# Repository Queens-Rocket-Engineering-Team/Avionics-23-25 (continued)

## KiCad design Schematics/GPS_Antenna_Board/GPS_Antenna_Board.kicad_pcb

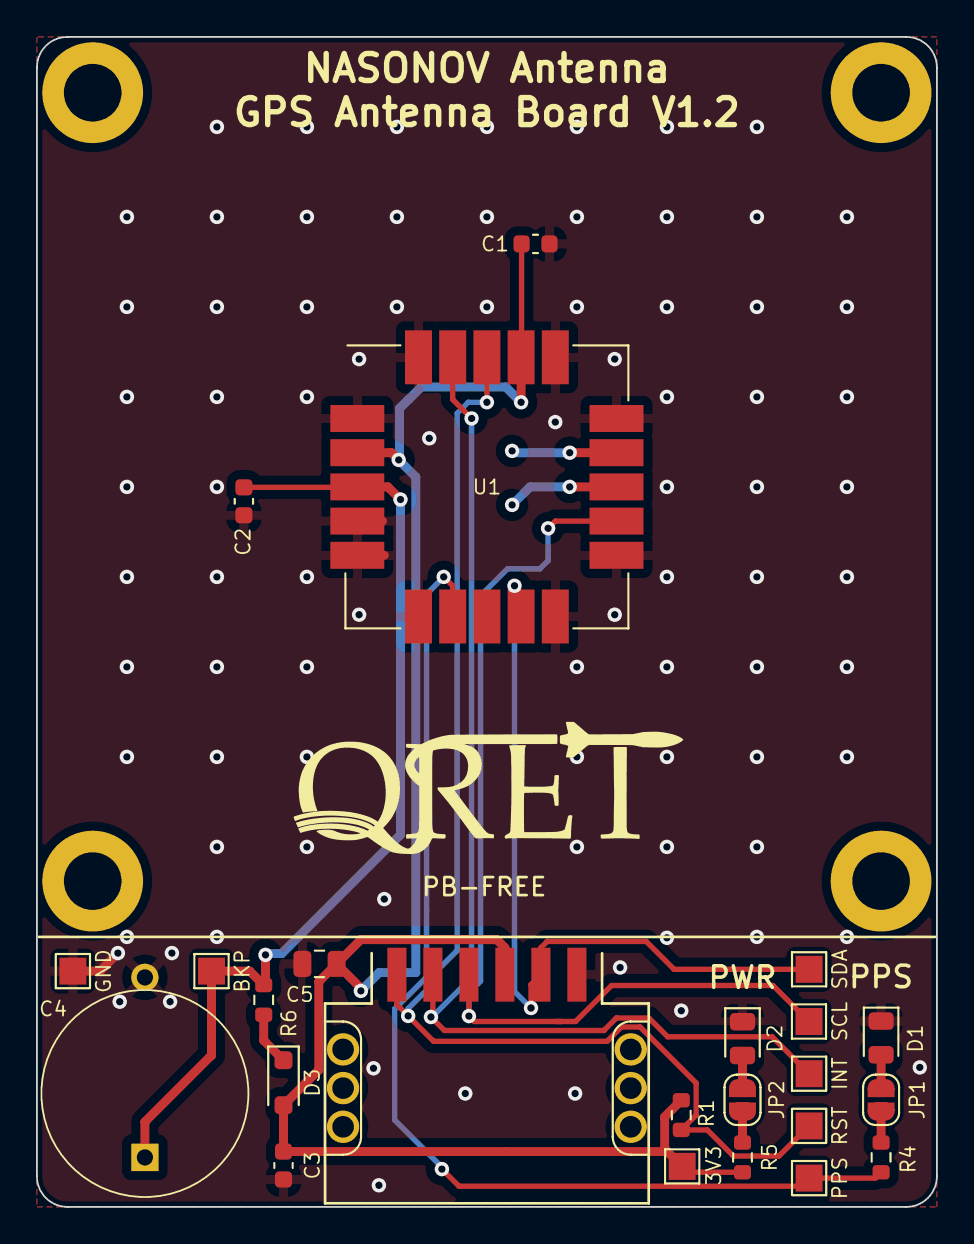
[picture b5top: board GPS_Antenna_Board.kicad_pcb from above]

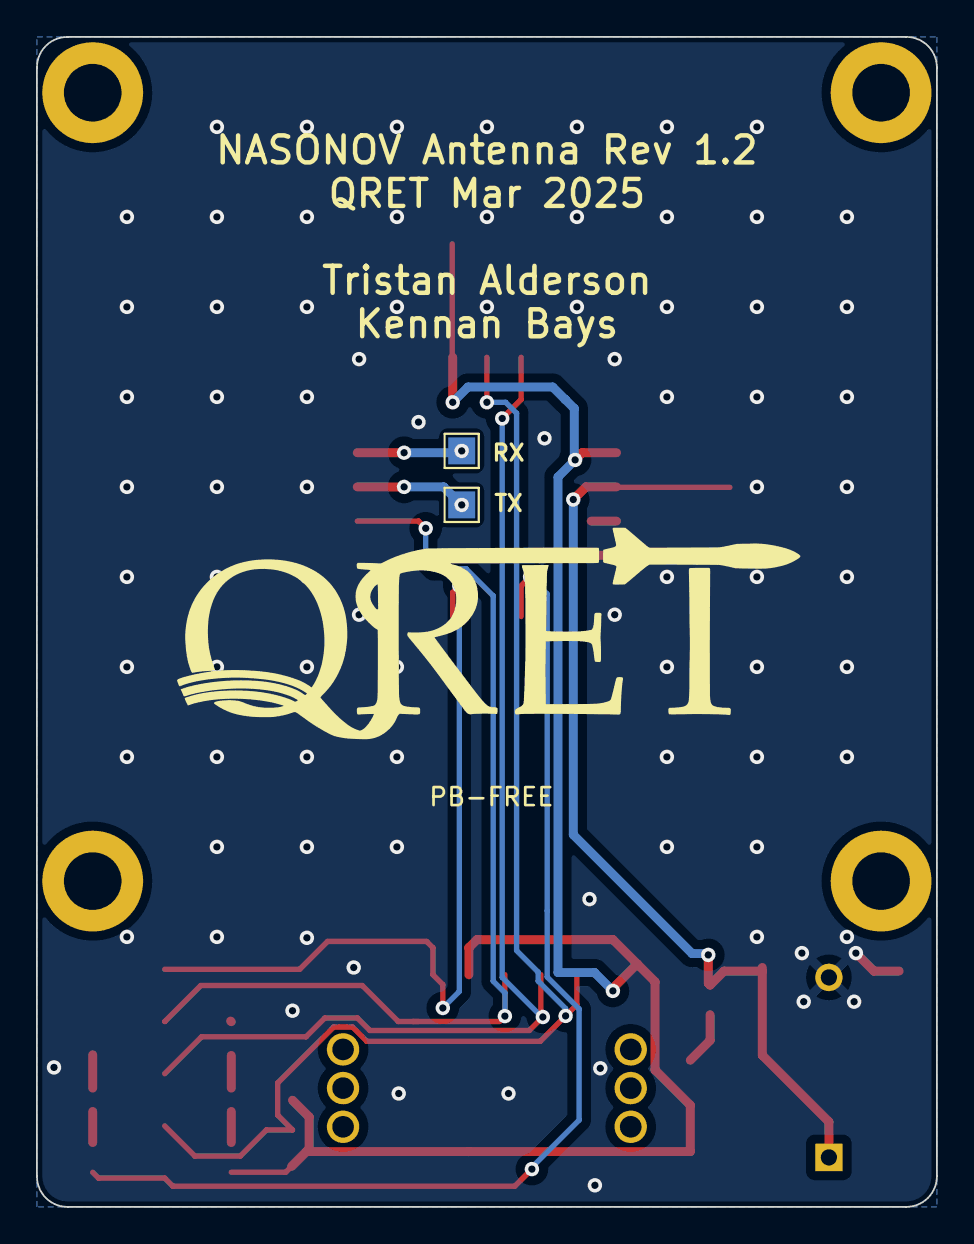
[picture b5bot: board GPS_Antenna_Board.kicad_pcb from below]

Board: 2 copper layers, 50.0 x 65.0 mm, 30 parts (2 on the bottom side), 15 nets.

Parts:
C1, C2: 100nF; C_0603_1608Metric
C3: 1uF; C_0603_1608Metric
C4: 330mF; CB5R5334HF-ZJP
C5: 47uF; C_0805_2012Metric
D1: White; LED_0805_2012Metric
D2: Green; LED_0805_2012Metric
D3: 1N5819WS; D_SOD-323_HandSoldering
H1, H2, H3, H4: MountingHole; MountingHole_3.2mm_M3_DIN965_Pad
J1: GT8E-6P-2H(55); CONN_GT8E-6P-2H(55)
JP1: ENA_PPS_LED; SolderJumper-2_P1.3mm_Open_RoundedPad1.0x1.5mm
JP2: ENA_PWR_LED; SolderJumper-2_P1.3mm_Open_RoundedPad1.0x1.5mm
R1: 10k; R_0603_1608Metric
R4: 2.2k; R_0603_1608Metric
R5: 3.3k; R_0603_1608Metric
R6: 100R; R_0603_1608Metric
TP1: GND; TestPoint_Pad_1.5x1.5mm
TP2: SCL; TestPoint_Pad_1.5x1.5mm
TP3: SDA; TestPoint_Pad_1.5x1.5mm
TP4: BKP; TestPoint_Pad_1.5x1.5mm
TP5: RST; TestPoint_Pad_1.5x1.5mm
TP6: INT; TestPoint_Pad_1.5x1.5mm
TP7: PPS; TestPoint_Pad_1.5x1.5mm
TP8: 3V3; TestPoint_Pad_1.5x1.5mm
TP9: RX; TestPoint_Pad_1.5x1.5mm
TP10: TX; TestPoint_Pad_1.5x1.5mm
U1: SAM-M10Q; ublox_SAM-M8Q_HandSolder

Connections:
+3.3V: C1.2, C3.1, C5.2, D3.2 (A), J1.3, R1.1, R5.1, TP8.1, U1.2 (VCC_IO), U1.17 (VCC)
BCKP_BATT: C2.2, C4.1, R6.2, TP4.1, U1.3 (V_BCKP)
GND: C1.1, C2.1, C3.2, C4.2, C5.1, D1.1 (K), D2.1 (K), J1.1, TP1.1, U1.1 (GND), U1.4 (GND), U1.5 (GND), U1.6 (GND), U1.10 (GND), U1.11 (GND), U1.15 (GND), U1.16 (GND), U1.20 (GND)
GPS_EXTINT: J1.5, TP6.1, U1.19 (EXTINT)
GPS_PPS: R4.1, TP7.1, U1.7 (TIMEPULSE)
GPS_RST: J1.6, R1.2, TP5.1, U1.18 (~RESET)
unnamed: D1.2 (A), JP1.1 (A)
unnamed: D2.2 (A), JP2.1 (A)
unnamed: D3.1 (K), R6.1
unnamed: JP1.2 (B), R4.2
unnamed: JP2.2 (B), R5.2
unnamed: TP9.1, U1.14 (RXD)
unnamed: TP10.1, U1.13 (TXD)
SCL: J1.4, TP2.1, U1.12 (SCL)
SDA: J1.2, TP3.1, U1.9 (SDA)

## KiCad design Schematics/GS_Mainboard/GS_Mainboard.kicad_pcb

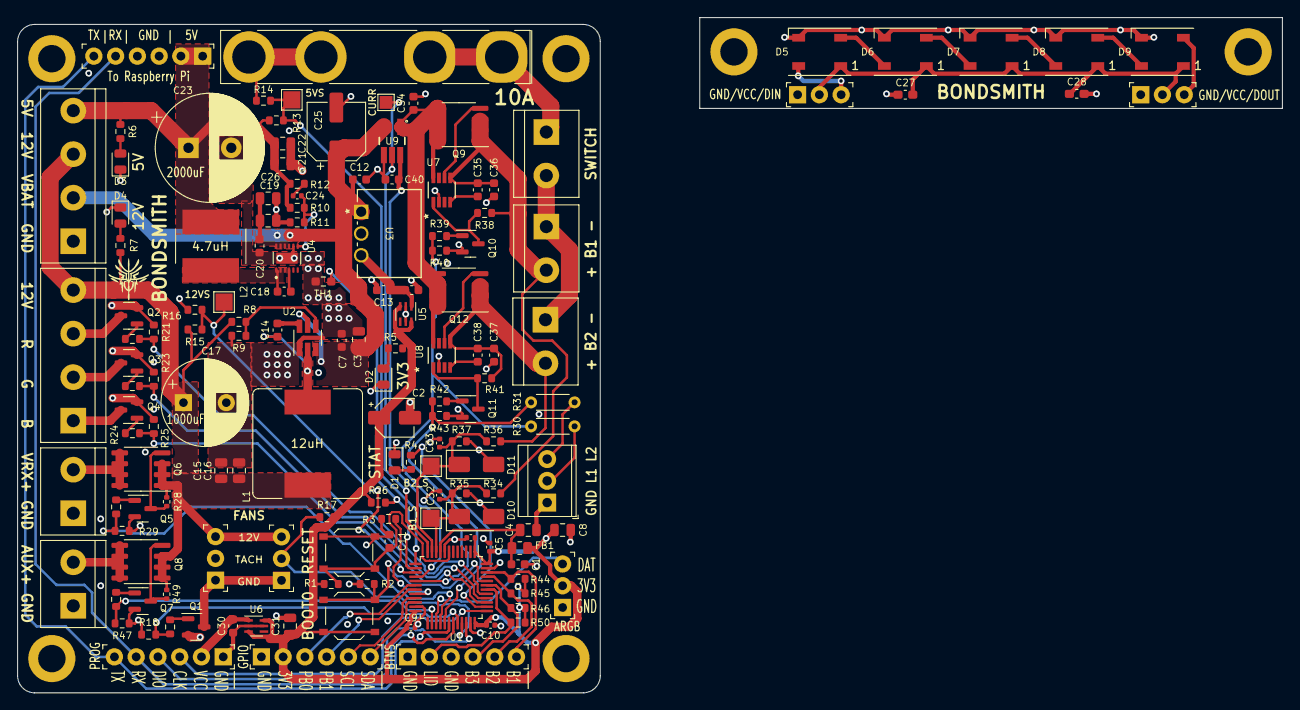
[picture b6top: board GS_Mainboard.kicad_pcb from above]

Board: 4 copper layers, 68.0 x 78.0 mm, 154 parts (0 on the bottom side), 89 nets.

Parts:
C1: 10n; C_0603_1608Metric
C2: 10uF; CP_Elec_4x5.4
C3, C19: 4.7uF; C_0805_2012Metric
C4, C8: 1uF; C_0805_2012Metric
C5, C6, C9, C10, C32, C33: 100n; C_0402_1005Metric
C7, C11, C14, C18, C20: 100nF; C_0603_1608Metric
C12: 10uF; C_0603_1608Metric
C13: 22uF; C_0603_1608Metric
C15, C16: 22uF; C_0805_2012Metric
C17: 1000uF, 25V; CP_Radial_D10.0mm_P5.00mm
C21, C22, C26, C31: 47uF; C_0805_2012Metric
C23: 2000uF, 25V; CP_Radial_D12.5mm_P5.00mm
C24: 33pF; C_0402_1005Metric
C25: 100uF; CP_Elec_6.3x5.9
C27, C28: 2.2uF; C_0603_1608Metric_Pad1.08x0.95mm_HandSolder
C29, C30, C34, C35, C36, C37, C38: 1uF; C_0603_1608Metric
C40: 0.1u; C_0603_1608Metric
D1: DB_LED (YLW); LED_0805_2012Metric
D2: 3.3V PWR (GRN); LED_0805_2012Metric
D3: 5.0V PWR (GRN); LED_0805_2012Metric
D4: 12V PWR (GRN); LED_0805_2012Metric
D5, D6, D7, D8, D9: WS2812B; LED_WS2812B_PLCC4_5.0x5.0mm_P3.2mm
D10, D11: SS54; D_SMA
F1: ATC Fuse; Fuseholder_Keystone_3555-2
FB1: 100R; R_0805_2012Metric
H1, H2, H3, H4, H5, H6: MountingHole; MountingHole_3.2mm_M3_ISO14580_Pad
J1: SWD Header; PinHeader_1x6_P2.54mm_Drill1.02mm
J2: RASPI; PinHeader_1x6_P2.54mm_Drill1.02mm
J3: ARGB_OUT; PinHeader_1x3_P2.54mm_Drill1.02mm
J4: RGB_IN; PinHeader_1x3_P2.54mm_Drill1.02mm
J5: RGB_OUT; PinHeader_1x3_P2.54mm_Drill1.02mm
J6: FAN1; PinHeader_1x3_P2.54mm_Drill1.02mm
J7: FAN2; PinHeader_1x3_P2.54mm_Drill1.02mm
J8: RGB12V; TerminalBlock_bornier-4_P5.08mm
J9: RTX_PWR; TerminalBlock_bornier-2_P5.08mm
J10: GPIO; PinHeader_1x6_P2.54mm_Drill1.02mm
J11: AUX_PWR; TerminalBlock_bornier-2_P5.08mm
J12: SRC_IND; TerminalBlock_TE_282834-3_1x03_P2.54mm_Horizontal
J13: BATT1; TerminalBlock_bornier-2_P5.08mm
J14: BATT2; TerminalBlock_bornier-2_P5.08mm
J15: SWITCH; TerminalBlock_bornier-2_P5.08mm
J16: BUTTS; PinHeader_1x6_P2.54mm_Drill1.02mm
J17: POWER; TerminalBlock_bornier-4_P5.08mm
L1: 12uH; L_Bourns_SRR1260
L2: 4.7uH; L_Bourns_SRN8040TA
Q1, Q2, Q3, Q4, Q5, Q7, Q10, Q11: AO3400A; SOT-23
Q6, Q8: AO4447A; SOIC-8_3.9x4.9mm_P1.27mm
Q9, Q12: AO4406A; SOIC-8_3.9x4.9mm_P1.27mm
R1, R17, R26, R35, R37, R38, R41, R44, R45, R46, R50: 10k; R_0603_1608Metric
R2, R3, R18, R21, R23, R25, R29, R40, R43, R47: 100k; R_0603_1608Metric
R4: 680R; R_0603_1608Metric
R5: 3.3k; R_0603_1608Metric
R6: 15k; R_0603_1608Metric
R7, R8: 68k; R_0603_1608Metric
R9: 3.6k; R_0603_1608Metric
R10: 33k; R_0603_1608Metric
R11: 6.2k; R_0603_1608Metric
R12: 1k; R_0603_1608Metric
R13, R14: 30k; R_0603_1608Metric
R15: 47k; R_0603_1608Metric
R16: 13k; R_0603_1608Metric
R19, R20, R22, R24, R27, R39, R42, R48: 510R; R_0603_1608Metric
R28, R49: 100k; R_0402_1005Metric
R30, R31: 1k; R_Axial_DIN0204_L3.6mm_D1.6mm_P5.08mm_Horizontal
R34, R36: 75k; R_0603_1608Metric
SW1: SW_STM_RESET; SW_Push_1P1T_XKB_TS-1187A
SW2: SW_STM_BOOT_MODE; SW_Push_1P1T_XKB_TS-1187A
TH1: 10k; R_0603_1608Metric_Pad0.98x0.95mm_HandSolder
TP1: 5VS; TestPoint_Pad_2.0x2.0mm
TP2: 12VS; TestPoint_Pad_2.0x2.0mm
TP3: B1_S; TestPoint_Pad_2.0x2.0mm
TP4: B2_S; TestPoint_Pad_2.0x2.0mm
TP5: CURR; TestPoint_Pad_1.5x1.5mm
U1: STM32F103C8T6; LQFP-48_7x7mm_P0.5mm
U2: LMR51430XDDCR; SOT-23-6_Handsoldering
U3: K78L03-500R3; K78Lxx-500R3_MNS_SIP3
U4: 296-LMR51450FNDRRRCT-ND; LMR51450SDRRR
U5, U6: LM66100DCKR; LMR66100_SC-70-6
U7, U8: LM74700QDDFRQ1; LM74700_SOT-23-THIN_1P6X2P9_TEX-M
U9: ACS37041KLHBLT-010B3; APS12628LLHALTBAP_HandSolder

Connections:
5V_SENSE: R13.1, R14.2, TP1.1, U1.13 (PA3)
12V_SENSE: R15.1, R16.2, TP2.1, U1.15 (PA5)
+3.3V: C2.1, C5.1, C6.1, C8.1, C9.1, C10.1, C31.1, FB1.2, J3.2, J10.2, R1.2, R5.1, R17.2, R26.1, R44.2, R45.2, R46.2, R50.2, SW2.2, U1.1 (VBAT), U1.24 (VDD), U1.36 (VDD), U1.48 (VDD), U5.3 (*CE), U5.6 (VOUT), U6.3 (*CE), U6.6 (VOUT)
+3.3VA: C1.1, C4.1, FB1.1, U1.9 (VDDA)
+5V: C21.1, C22.1, C23.1, J2.1, J2.2, J17.4, L2.2, R6.1, R10.1, R12.1, R13.2
+12V: C15.1, C16.1, C17.1, J6.3, J7.3, J8.4, J17.3, L1.2, Q6.1 (S), Q6.2 (S), Q6.3 (S), Q8.1 (S), Q8.2 (S), Q8.3 (S), R7.1, R8.1, R15.2, R28.1, R49.1
+BATT: C3.1, C7.1, C12.1, C19.1, C20.1, C25.1, C26.1, J17.2, U2.3 (VIN), U2.5 (EN), U3.1 (VI), U4.9 (EN), U4.10 (VIN), U4.11 (VIN__1), U4.12 (VIN__2), U9.2 (IP-)
/5V_FB: C24.2, R10.2, R11.1, U4.7 (FB)
/5V_L_A: C18.1, L2.1, U4.1 (SW), U4.2 (SW__1), U4.3 (SW__2)
/12V_FB: R8.2, R9.1, U2.4 (FB)
/AUX+: J11.2, Q8.5 (D), Q8.6 (D), Q8.7 (D), Q8.8 (D)
/B: J8.1, Q4.3 (D)
/B1_EN: J12.2, R30.1
/B2_EN: J12.3, R31.1
/G: J8.2, Q3.3 (D)
/R: J8.3, Q2.3 (D)
/VRX+: J9.2, Q6.5 (D), Q6.6 (D), Q6.7 (D), Q6.8 (D)
AUX_PWR: R47.2, R48.2, U1.26 (PB13)
BATT1_EN: R30.2, R39.1, R40.2, U1.17 (PA7)
BATT1_RAW: C35.1, C36.1, J13.2, Q9.1 (S), Q9.2 (S), Q9.3 (S), R34.1, R38.1, U7.5 (ANODE)
BATT2_EN: R31.2, R42.1, R43.2, U1.29 (PA8)
BATT2_RAW: C37.1, C38.1, J14.2, Q12.1 (S), Q12.2 (S), Q12.3 (S), R36.1, R41.1, U8.5 (ANODE)
BATT_1_SENSE: C32.1, D10.1 (K), R34.2, R35.1, TP3.1, U1.10 (PA0)
BATT_2_SENSE: C33.1, D11.1 (K), R36.2, R37.1, TP4.1, U1.11 (PA1)
BATT_COM: C34.1, Q9.5 (D), Q9.6 (D), Q9.7 (D), Q9.8 (D), Q12.5 (D), Q12.6 (D), Q12.7 (D), Q12.8 (D), U7.8 (CATHODE), U8.8 (CATHODE), U9.1 (IP+)
BOOT0: R2.2, SW2.1, U1.44 (BOOT0)
BOOT1: R3.2, U1.20 (PB2)
BUTT_1: J16.6, R44.1, U1.46 (PB9)
BUTT_2: J16.5, R45.1, U1.45 (PB8)
BUTT_3: J16.4, R46.1, U1.43 (PB7)
CURR_PWR: C40.1, U1.16 (PA6), U9.5 (VDD)
CURR_SENSE: TP5.1, U1.12 (PA2), U9.4 (VOUT)
DB_LED: R4.2, U1.38 (PA15)
FAN_PWM: R18.2, R19.1, U1.32 (PA11)
FAN_TACH: J6.2, R17.1, U1.33 (PA12)
GND: C1.2, C2.2, C3.2, C4.2, C5.2, C6.2, C7.2, C8.2, C9.2, C10.2, C11.2, C12.2, C13.2, C15.2, C16.2, C17.2, C19.2, C20.2, C21.2, C22.2, C23.2, C25.2, C26.2, C29.2, C30.2, C31.2, C32.2, C33.2, C34.2, C36.2, C37.2, C40.2, D1.1 (K), D2.1 (K), D3.1 (K), D4.1 (K), D10.2 (A), D11.2 (A), F1.2, J1.1, J2.3, J2.4, J3.1, J9.1, J10.1, J11.1, J12.1, J16.1, J16.3, J17.1, Q1.2 (S), Q2.2 (S), Q3.2 (S), Q4.2 (S), Q5.2 (S), Q7.2 (S), Q10.2 (S), Q11.2 (S), R2.1, R3.1, R9.2, R11.2, R14.1, R16.1, R18.1, R21.1, R23.1, R25.1, R29.1, R35.2, R37.2, R40.1, R43.1, R47.1, SW1.1, TH1.2, U1.8 (VSSA), U1.23 (VSS), U1.35 (VSS), U1.47 (VSS), U2.1 (GND), U3.2 (GND), U4.8 (AGND), U4.13 (PGND), U5.2 (GND), U5.5 (ST), U6.2 (GND), U6.5 (ST), U7.2 (GND), U8.2 (GND), U9.3 (GND)
LID_SENSE: J16.2, R50.1, U1.42 (PB6)
unnamed: C24.1, R12.2
unnamed: D1.2 (A), R4.1
unnamed: D2.2 (A), R5.2
unnamed: D3.2 (A), R6.2
unnamed: D4.2 (A), R7.2
unnamed: D5.2 (DOUT), D6.4 (DIN)
unnamed: D6.2 (DOUT), D7.4 (DIN)
unnamed: D7.2 (DOUT), D8.4 (DIN)
unnamed: D8.2 (DOUT), D9.4 (DIN)
unnamed: J13.1, J14.1, J15.2
unnamed: F1.1, J15.1
unnamed: J6.1, J7.1, Q1.3 (D)
unnamed: Q1.1 (G), R19.2
unnamed: Q2.1 (G), R20.2
unnamed: Q3.1 (G), R22.2
unnamed: Q4.1 (G), R24.2
unnamed: Q5.3 (D), Q6.4 (G), R28.2
unnamed: Q5.1 (G), R27.1
unnamed: Q7.3 (D), Q8.4 (G), R49.2
unnamed: Q7.1 (G), R48.1
unnamed: Q9.4 (G), U7.6 (GATE)
unnamed: Q10.3 (D), R38.2, U7.1 (EN)
unnamed: Q10.1 (G), R39.2
unnamed: Q11.3 (D), R41.2, U8.1 (EN)
unnamed: Q11.1 (G), R42.2
unnamed: Q12.4 (G), U8.6 (GATE)
unnamed: C14.2, U2.6 (CB)
unnamed: C14.1, L1.1, U2.2 (SW)
unnamed: C18.2, U4.4 (BOOT)
unnamed: C35.2, U7.4 (VCAP)
unnamed: C38.2, U8.4 (VCAP)
PB0: J10.3, U1.18 (PB0)
PB1: J10.4, U1.19 (PB1)
PSU_TEMP: R26.2, TH1.1, U1.14 (PA4)
RGB12_B: R24.1, R25.2, U1.39 (PB3)
RGB12_G: R22.1, R23.2, U1.40 (PB4)
RGB12_R: R20.1, R21.2, U1.41 (PB5)
RGB_DATA: J3.3, U1.27 (PB14)
RGB_DATA_IN: D5.4 (DIN), J4.3
RGB_DATA_OUT: D9.2 (DOUT), J5.3
RGB_GND: C27.1, C28.1, D5.3 (VSS), D6.3 (VSS), D7.3 (VSS), D8.3 (VSS), D9.3 (VSS), J4.1, J5.1
RGB_V+: C27.2, C28.2, D5.1 (VDD), D6.1 (VDD), D7.1 (VDD), D8.1 (VDD), D9.1 (VDD), J4.2, J5.2
RX: J1.5, J2.5, U1.31 (PA10)
SCL: J10.5, U1.21 (PB10)
SDA: J10.6, U1.22 (PB11)
STM_RESET: C11.1, R1.1, SW1.2, U1.7 (NRST)
SWCLK: J1.3, U1.37 (PA14)
SWDIO: J1.4, U1.34 (PA13)
TX: J1.6, J2.6, U1.30 (PA9)
VRX_PWR: R27.2, R29.2, U1.28 (PB15)
V_BUCK: C13.1, C29.1, U3.3 (VO), U5.1 (VIN)
V_SWD: C30.1, J1.2, U6.1 (VIN)

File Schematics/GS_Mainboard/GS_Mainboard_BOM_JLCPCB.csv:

Comment,Designator,Footprint,LCSC Part #
10n Unpolarized capacitor,C1,C_0603_1608Metric,C57112
4.7uF Unpolarized capacitor,"C3,C19",C_0805_2012Metric,C1779
1uF Polarized capacitor,"C4,C8",C_0805_2012Metric,C28323
100n Unpolarized capacitor,"C5,C6,C9,C10,C32,C33",C_0402_1005Metric,C1525
100nF Unpolarized capacitor,"C7,C11,C14,C18,C20",C_0603_1608Metric,C14663
10uF Unpolarized capacitor,C12,C_0603_1608Metric,C19702
22uF Unpolarized capacitor,C13,C_0603_1608Metric,C59461
22uF Unpolarized capacitor,"C15,C16",C_0805_2012Metric,C45783
47uF Unpolarized capacitor,"C21,C22,C26,C31",C_0805_2012Metric,C16780
33pF Unpolarized capacitor,C24,C_0402_1005Metric,C1562
1uF Unpolarized capacitor,"C29,C30,C34,C35,C36,C37,C38,C39",C_0603_1608Metric,C15849
0.1u Unpolarized capacitor,C40,C_0603_1608Metric,C14663
DB_LED (YLW) Light emitting diode,D1,LED_0603_1608Metric,C72038
3.3V PWR (GRN) Light emitting diode,D2,LED_0805_2012Metric,C2297
5.0V PWR (GRN) Light emitting diode,D3,LED_0805_2012Metric,C2297
12V PWR (GRN) Light emitting diode,D4,LED_0805_2012Metric,C2297
100R Ferrite bead,FB1,R_0805_2012Metric,C1015
"AO3400A 30V Vds, 5.7A Id, N-Channel MOSFET, SOT-23","Q1,Q2,Q3,Q4,Q5,Q10,Q11",SOT-23,C20917
"AO4447A -6.7A Id, -20V Vds, P-Channel HEXFET Power MOSFET, SO-8","Q6,Q7,Q8",SOIC-8_3.9x4.9mm_P1.27mm,C125867
"AO4406A 9.7A Id, 30V Vds, N-Channel HEXFET Power MOSFET, SO-8","Q9,Q12",SOIC-8_3.9x4.9mm_P1.27mm,C5155213
10k Resistor,"R1,R17,R26,R35,R37,R38,R41,R44,R45,R46",R_0603_1608Metric,C25804
100k Resistor,"R2,R3,R18,R21,R23,R25,R29,R40,R43",R_0603_1608Metric,C25803
680R Resistor,R4,R_0603_1608Metric,C23228
3.3k Resistor,R5,R_0603_1608Metric,C22978
15k Resistor,"R6,R32,R33",R_0603_1608Metric,C22809
68k Resistor,"R7,R8",R_0603_1608Metric,C23231
3.6k Resistor,R9,R_0603_1608Metric,C22980
33k Resistor,R10,R_0603_1608Metric,C4216
6.2k Resistor,R11,R_0603_1608Metric,C4260
1k Resistor,R12,R_0603_1608Metric,C21190
30k Resistor,"R13,R14",R_0603_1608Metric,C22984
47k Resistor,R15,R_0603_1608Metric,C25819
13k Resistor,R16,R_0603_1608Metric,C22797
510R Resistor,"R19,R20,R22,R24,R27,R39,R42",R_0603_1608Metric,C23193
100k Resistor,R28,R_0402_1005Metric,C25741
75k Resistor,"R34,R36",R_0603_1608Metric,C23242
"SW_STM_RESET Push button switch, generic, two pins",SW1,SW_Push_1P1T_XKB_TS-1187A,C318884
"SW_STM_BOOT_MODE Push button switch, generic, two pins",SW2,SW_Push_1P1T_XKB_TS-1187A,C318884
"STM32F103C8T6 STMicroelectronics Arm Cortex-M3 MCU, 64KB flash, 20KB RAM, 72 MHz, 2.0-3.6V, 37 GPIO, LQFP48",U1,LQFP-48_7x7mm_P0.5mm,C8734
LM66100DCKR ,"U5,U6",LMR66100_SC-70-6,C2869734
